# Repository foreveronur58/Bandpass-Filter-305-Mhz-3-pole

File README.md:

# Bandpass-Filter-305-Mhz-3-pole
Aim: 305 MHz, 3 resonance capacative coupled LC band pass filter with LTSpiece

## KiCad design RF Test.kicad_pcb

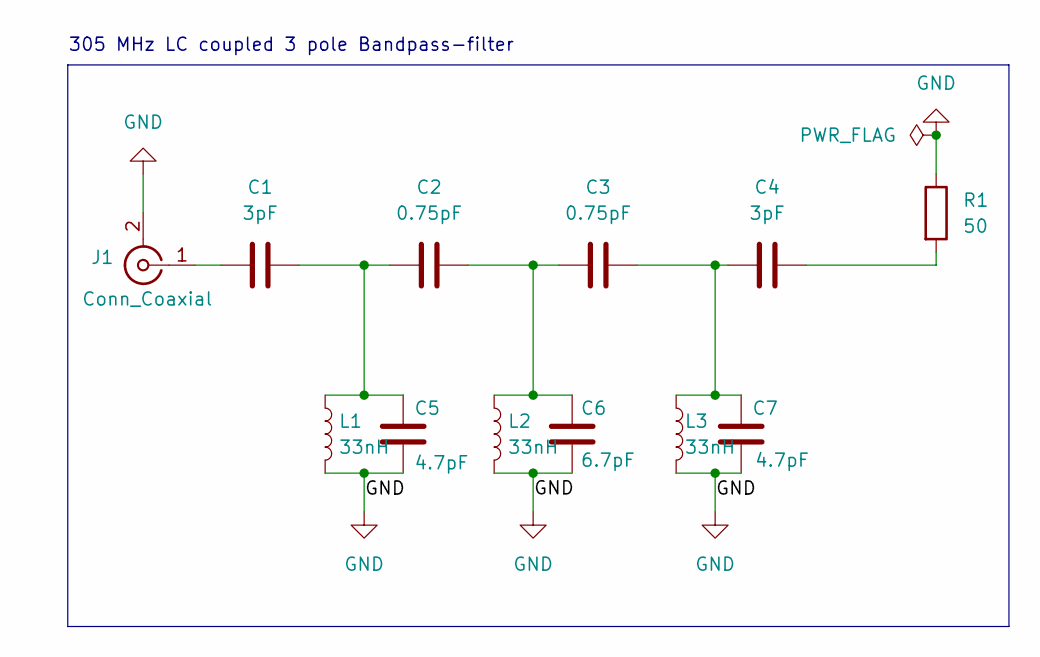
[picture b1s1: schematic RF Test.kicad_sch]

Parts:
C1, C4: 3pF; CAPC1608X90N; MPN GRM1885C1H3R0BZ01D
C2, C3: 0.75pF; CAPC1608X90; MPN CC0603BRNPO9BNR75
C5, C7: 4.7pF; CAPC1608X87N; MPN VJ0603A4R7BXACW1BC
C6: 6.7pF; CAPC1608X90N; MPN GRM1886T1H6R7DD01D
J1: Conn_Coaxial; SMA_Samtec_SMA-J-P-H-ST-EM1_EdgeMount; MPN SMA-J-P-H-ST-EM1
L1, L2, L3: 33nH; INDC1608X100N; MPN LQW18AN33NG00D
R1: 50; R_0603_1608Metric; MPN RCP0603W50R0GEB

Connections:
GND: C5.2, C6.2, C7.2, J1.2 (Ext), L1.2, L2.2, L3.2, R1.1
unnamed: C1.2, C2.1, C5.1, L1.1
unnamed: C2.2, C3.2, C6.1, L2.1
unnamed: C3.1, C4.1, C7.1, L3.1
unnamed: C4.2, R1.2
unnamed: C1.1, J1.1 (In)

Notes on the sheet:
305 MHz LC coupled 3 pole Bandpass-filter

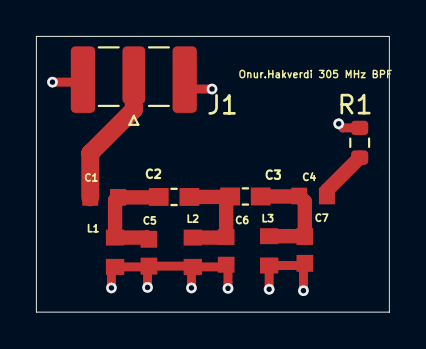
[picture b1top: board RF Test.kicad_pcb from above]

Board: 2 copper layers, 19.6 x 15.3 mm, 12 parts (0 on the bottom side), 6 nets.

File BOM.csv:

Reference;Qty;Value;Footprint;Datasheet;Manufacturer;MPN
C1,C4;2;3pF;GRM1885C1H3R0BZ01D_3pF0603:CAPC1608X90N;;Murata;GRM1885C1H3R0BZ01D
C2,C3;2;0.75pF;CC0603BRNPO9BNR75_0.75pF063:CAPC1608X90;;Yageo;CC0603BRNPO9BNR75
C5,C7;2;4.7pF;VJ0603A4R7BXACW1BC_4.7pF0603:CAPC1608X87N;;Vishay;VJ0603A4R7BXACW1BC
C6;1;6.7pF;GRM1886T1H6R7DD01D_6.7pF0603:CAPC1608X90N;;Murata;GRM1886T1H6R7DD01D
J1;1;Conn_Coaxial;Connector_Coaxial:SMA_Samtec_SMA-J-P-H-ST-EM1_EdgeMount;; Samtec;SMA-J-P-H-ST-EM1
L1,L2,L3;3;33nH;LQW18AN33NG00D_33nH:INDC1608X100N;;Murata;LQW18AN33NG00D
R1;1;50;Resistor_SMD:R_0603_1608Metric;;Vishay;RCP0603W50R0GEB
